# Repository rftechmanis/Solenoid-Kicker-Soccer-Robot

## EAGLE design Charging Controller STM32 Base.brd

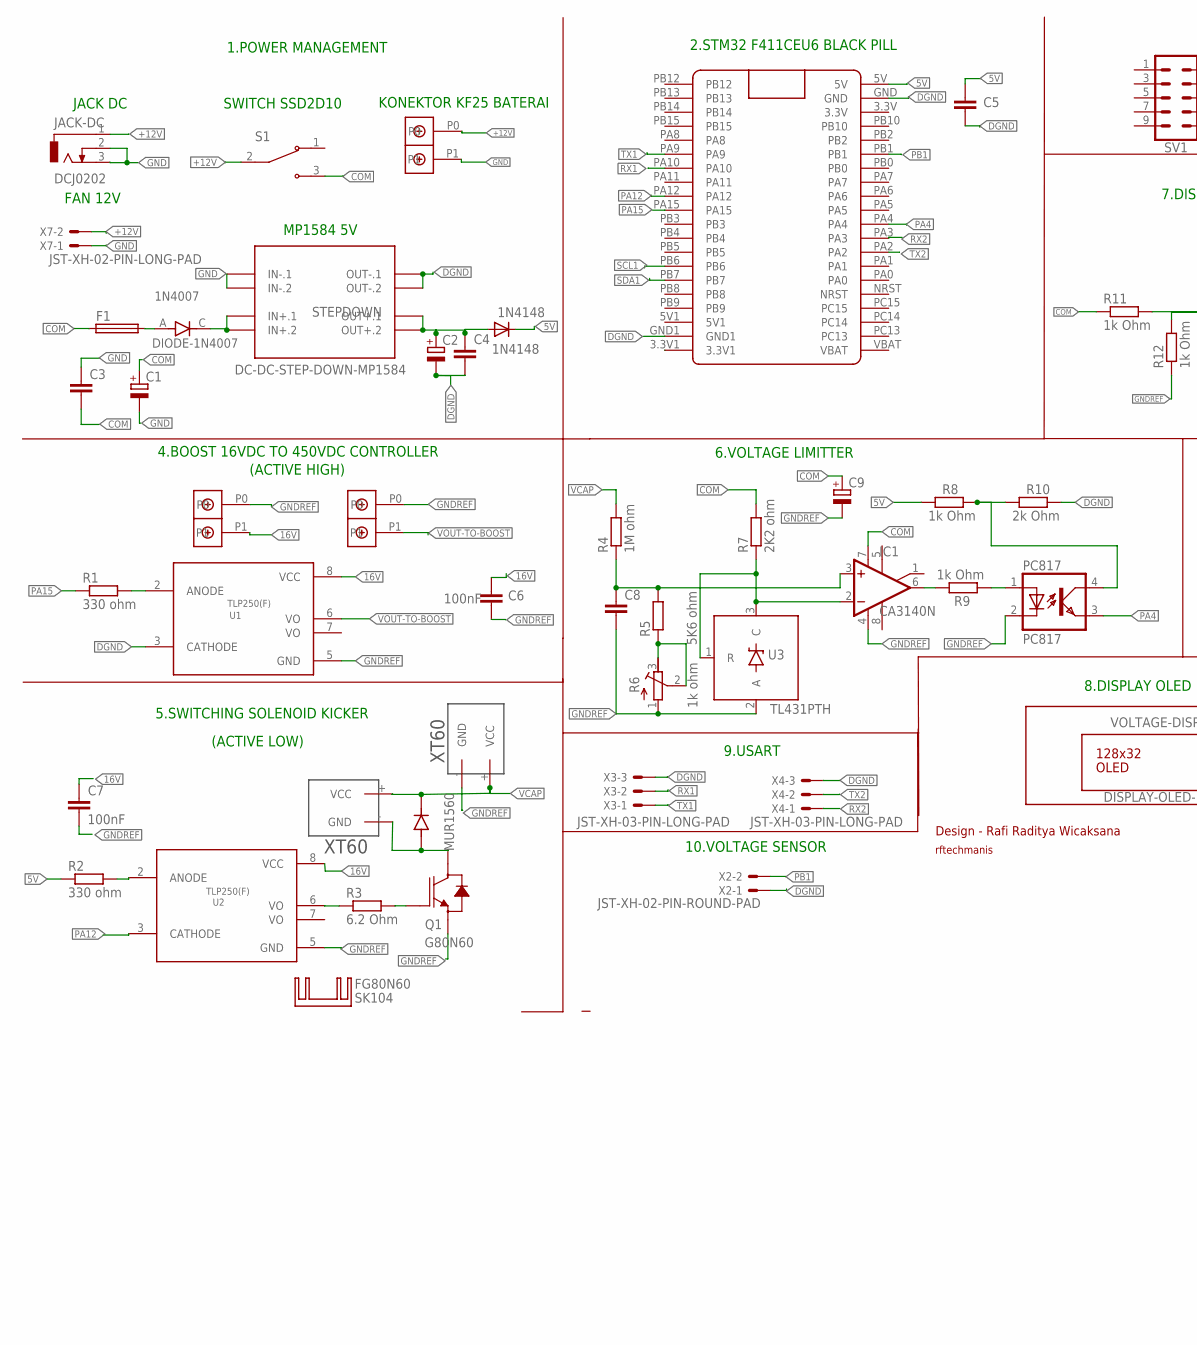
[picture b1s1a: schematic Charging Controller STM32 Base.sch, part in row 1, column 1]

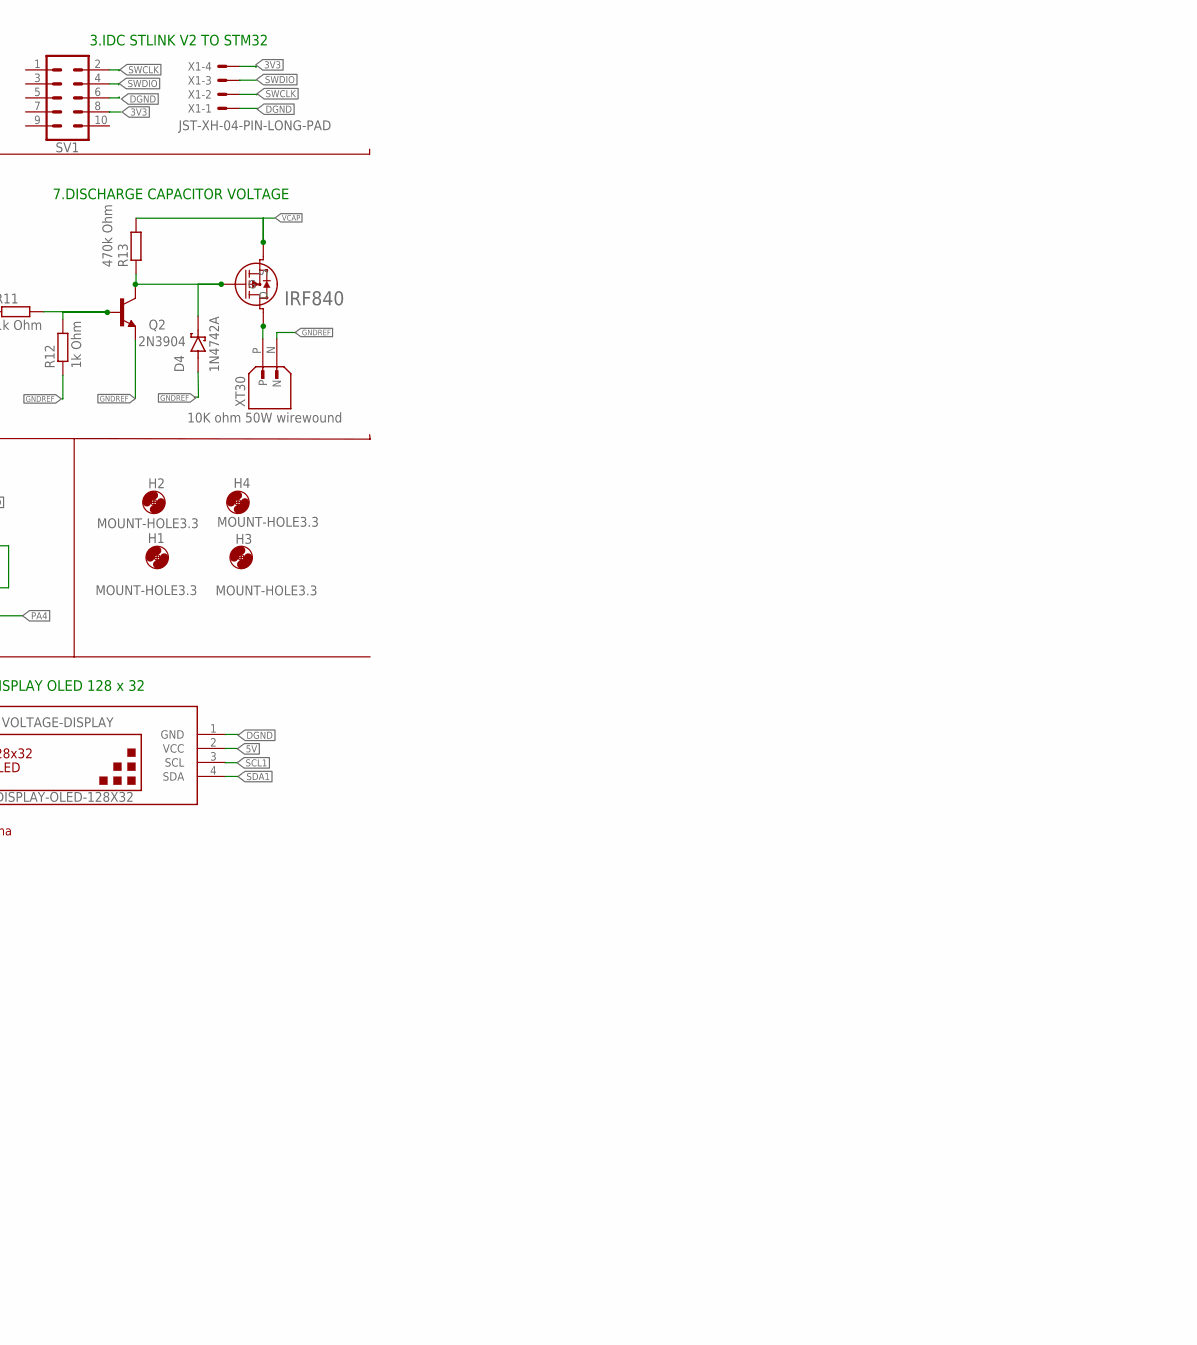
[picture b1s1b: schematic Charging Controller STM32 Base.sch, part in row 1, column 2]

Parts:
1N4007: DIODE-1N4007; DIOAD1060W80L520D270
1N4148: 1N4148; DO35-10
C1, C2: CPOL-EUE3.5-8; E3,5-8
C3, C4, C5: C-EU050-030X075; C050-030X075
C6, C7: 100nF; C050-030X075
C8: C-EU050-035X075; C050-035X075
C9: CPOL-EUE2-5; E2-5
D4: 1N4742A; DIOAD1036W78L463D237
F1: SH25
FG80N60: SK104
H1, H2, H3, H4: MOUNT-HOLE3.3; 3,3
IC1: CA3140N; DIL08
JACK-DC: DCJ0202
KF25_2PIN3, KF25_2PIN4: KF25_2PIN
MUR1560: MUR1560; TO508P997X444X1905-2
PC817: PC817; DIL04
Q1: G80N60; TO544P1613X521X2557-3
Q2: 2N3904; TO92
R1, R2: 330 ohm; 0204/7
R3: 6.2 Ohm; 0411/12
R4: 1M ohm; 0411/12
R5: 5K6 ohm; 0411/12
R6: 1k ohm; RTRIM64X
R7: 2K2 ohm; 0207/10
R8, R9: 1k Ohm; 0207/10
R10: 2k Ohm; 0207/10
R11, R12: 1k Ohm; 0204/7
R13: 470k Ohm; 0204/7
S1: 1103M2S3CQE2; SW_1103M2S3CQE2
STEPDOWN: DC-DC-STEP-DOWN-MP1584
SV1: ML10
U1, U2: TLP250(F); DIP1016W50P254L966H380Q8P
U3: TL431PTH; TO-92
U4: IRF840; TO220AB_VIS
U$2: KF25_2PIN
U$3: BLACK_PILL
U$4, U$5: XT60
VOLTAGE-DISPLAY: DISPLAY-OLED-128X32
X1: JST-XH-04-PIN-LONG-PAD; JST-XH-04-PACKAGE-LONG-PAD
X2: JST-XH-02-PIN-ROUND-PAD; JST-XH-02-PACKAGE-ROUND-PAD
X3, X4: JST-XH-03-PIN-LONG-PAD; JST-XH-03-PACKAGE-LONG-PAD
X7: JST-XH-02-PIN-LONG-PAD; JST-XH-02-PACKAGE-LONG-PAD
XT30: 10K ohm 50W wirewound; AMASS_XT30PW-M

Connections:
3,3V: PC817.4 (COL), R8.2, R10.1
3.3V: U$3.3.3V1
3V3: SV1.8, X1.4
5V: 1N4148.C, C5.1, R2.1, R8.1, U$3.5V, VOLTAGE-DISPLAY.2 (VCC)
16V: C6.1, C7.1, KF25_2PIN3.P1, U1.8 (VCC), U2.8 (VCC)
+12V: JACK-DC.1, S1.2, U$2.P0, X7.2
COM: C1.+, C3.2, C9.+, F1.1, IC1.7 (V+), R7.2, R11.1, S1.3
DGND: C2.-, C4.2, C5.2, R10.2, STEPDOWN.OUT-.1, STEPDOWN.OUT-.2, SV1.6, U1.3 (CATHODE), U$3.GND, U$3.GND1, VOLTAGE-DISPLAY.1 (GND), X1.1, X2.1, X3.3, X4.3
GND: C1.-, C3.1, JACK-DC.2, JACK-DC.3, STEPDOWN.IN-.1, STEPDOWN.IN-.2, U$2.P1, X7.1
GNDREF: C6.2, C7.2, C8.2, C9.-, D4.2 (A), IC1.4 (V-), KF25_2PIN3.P0, KF25_2PIN4.P0, PC817.2 (C), Q1.3 (E), Q2.3 (E), R6.1 (A), R12.1, U1.5 (GND), U2.5 (GND), U3.2 (A), U$4.- (GND), XT30.N
unnamed: 1N4007.C, STEPDOWN.IN+.1, STEPDOWN.IN+.2
unnamed: 1N4007.A, F1.2
unnamed: R1.2, U1.2 (ANODE)
unnamed: 1N4148.A, C2.+, C4.1, STEPDOWN.OUT+.1, STEPDOWN.OUT+.2
unnamed: R2.2, U2.2 (ANODE)
unnamed: MUR1560.3 (A), Q1.2 (C), U$5.- (GND)
unnamed: R3.1, U2.6 (VO)
unnamed: Q1.1 (G), R3.2
unnamed: C8.1, IC1.3 (+IN), R4.1, R5.2
unnamed: R5.1, R6.2 (S), R6.3 (E)
unnamed: IC1.2 (-IN), R7.1, U3.1 (R), U3.3 (C)
unnamed: IC1.6 (OUT), R9.2
unnamed: PC817.1 (A), R9.1
unnamed: Q2.2 (B), R11.2, R12.2
unnamed: D4.1 (K), Q2.1 (C), R13.1, U4.1 (G)
unnamed: U4.2 (D), XT30.P
PA4: PC817.3 (EMIT), U$3.PA4
PA12: U2.3 (CATHODE), U$3.PA12
PA15: R1.1, U$3.PA15
PB1: U$3.PB1, X2.2
RX1: U$3.PA10, X3.2
RX2: U$3.PA3, X4.1
SCL1: U$3.PB6, VOLTAGE-DISPLAY.3 (SCL)
SDA1: U$3.PB7, VOLTAGE-DISPLAY.4 (SDA)
SWCLK: SV1.2, X1.2
SWDIO: SV1.4, X1.3
TX1: U$3.PA9, X3.1
TX2: U$3.PA2, X4.2
VCAP: MUR1560.1 (K), R4.2, R13.2, U4.3 (S), U$4.+ (VCC), U$5.+ (VCC)
VOUT-TO-BOOST: KF25_2PIN4.P1, U1.6 (VO)

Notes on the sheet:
1.POWER MANAGEMENT
KONEKTOR KF25 BATERAI
FAN 12V
JACK DC
SWITCH SSD2D10
3.IDC STLINK V2 TO STM32
RAFI RADITYA WICAKSANA
POLITEKNIK NEGERI SEMARANG
MP1584 5V
2.STM32 F411CEU6 BLACK PILL
Design - Rafi Raditya Wicaksana
rftechmanis
8.DISPLAY OLED 128 x 32
4.BOOST 16VDC TO 450VDC CONTROLLER
5.SWITCHING SOLENOID KICKER
6.VOLTAGE LIMITTER
7.DISCHARGE CAPACITOR VOLTAGE
(ACTIVE LOW)
(ACTIVE HIGH)
9.USART
10.VOLTAGE SENSOR

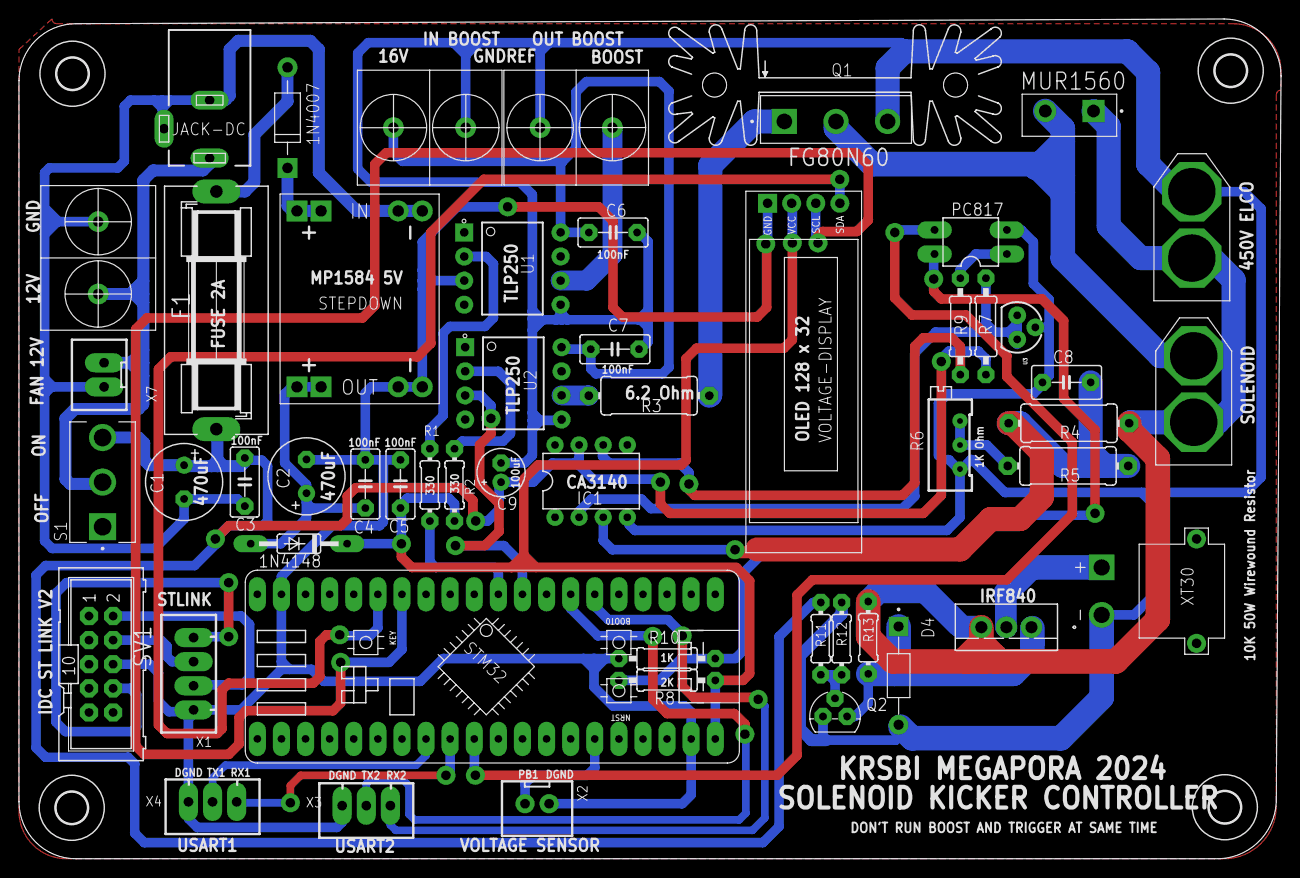
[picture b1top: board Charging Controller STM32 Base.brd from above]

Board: 2 copper layers, 133.0 x 88.5 mm, 57 parts (0 on the bottom side), 39 nets.

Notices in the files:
parts and their libraries:
diy-modules: Released under the Creative Commons Attribution 4.0 International License: http://creativecommons.org/licenses/by/4.0
COPYRIGHT: Copyright (C) 2026 Ultra Librarian. All rights reserved.
